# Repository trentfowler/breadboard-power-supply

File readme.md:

# Breadboard power supply

**Description:** Breadboard power supply that delivers 3.3v/5v

BOM - https://www.digikey.com/short/pfpr05

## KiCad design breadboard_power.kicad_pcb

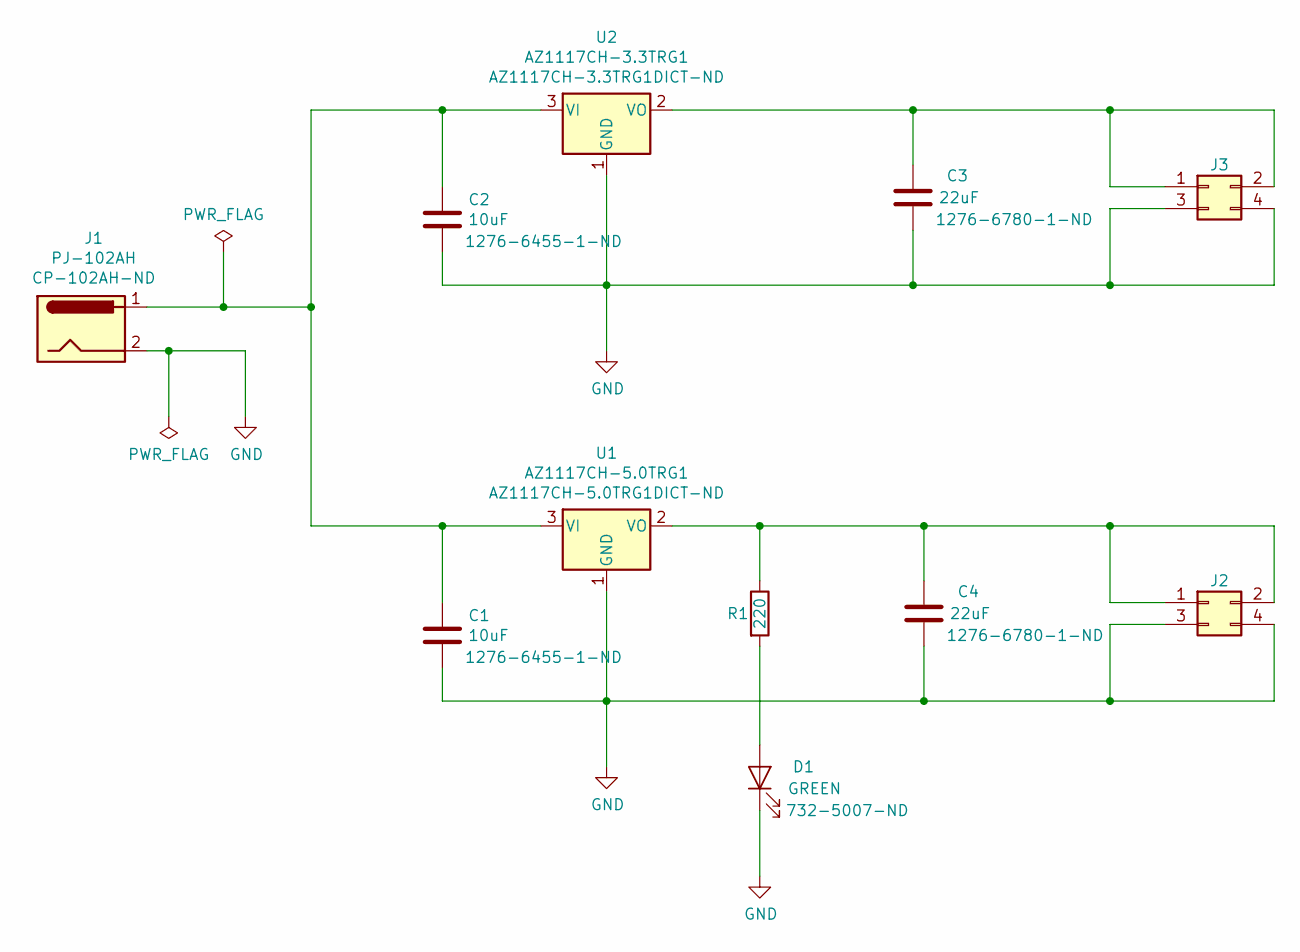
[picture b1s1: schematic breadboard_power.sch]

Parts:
C1, C2: 10uF; C_0805_2012Metric_Pad1.15x1.40mm_HandSolder; digikey 1276-6455-1-ND
C3, C4: 22uF; C_0805_2012Metric_Pad1.15x1.40mm_HandSolder; digikey 1276-6780-1-ND
D1: GREEN; LED_D3.0mm; digikey 732-5007-ND
J1: PJ-102AH; BarrelJack_CUI_PJ-102AH_Horizontal; digikey CP-102AH-ND
J2, J3: Conn_02x02_Odd_Even; PinHeader_2x02_P2.54mm_Vertical
R1: 220; R_0805_2012Metric_Pad1.15x1.40mm_HandSolder
U1: AZ1117CH-5.0TRG1; SOT-223-3_TabPin2; digikey AZ1117CH-5.0TRG1DICT-ND
U2: AZ1117CH-3.3TRG1; SOT-223-3_TabPin2; digikey AZ1117CH-3.3TRG1DICT-ND

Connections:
GND: C1.2, C2.2, C3.2, C4.2, D1.1 (K), J1.2, J2.3, J2.4, J3.3, J3.4, U1.1 (GND), U2.1 (GND)
unnamed: C1.1, C2.1, J1.1, U1.3 (VI), U2.3 (VI)
unnamed: C3.1, J3.1, J3.2, U2.2 (VO)
unnamed: C4.1, J2.1, J2.2, R1.1, U1.2 (VO)
unnamed: D1.2 (A), R1.2

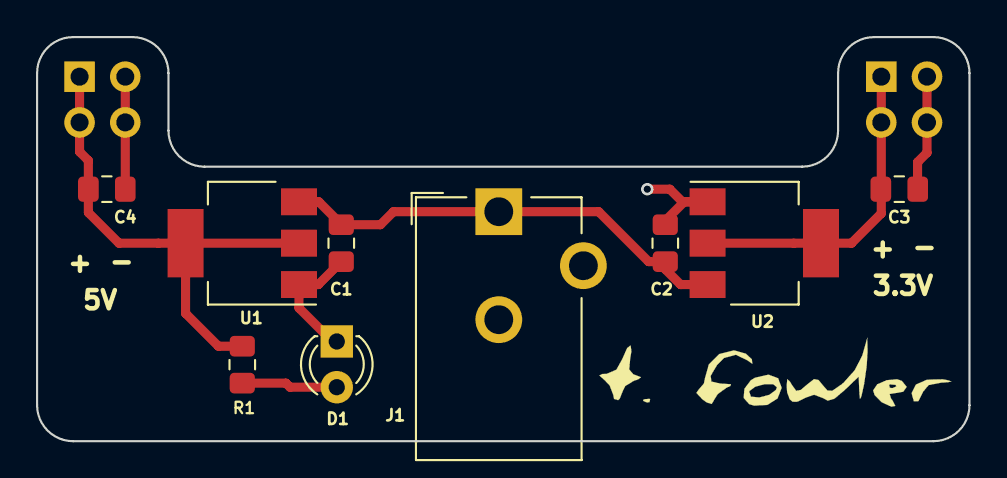
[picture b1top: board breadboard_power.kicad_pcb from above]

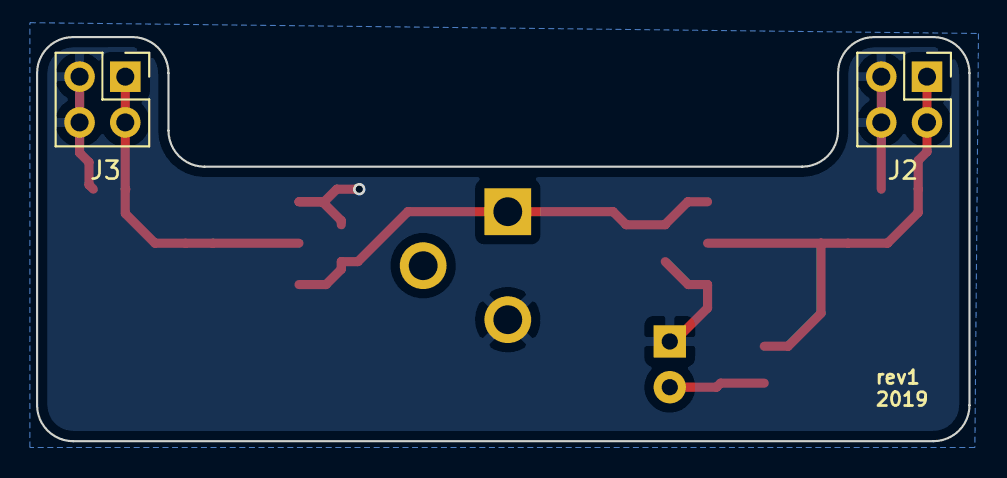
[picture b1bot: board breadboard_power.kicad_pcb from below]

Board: 2 copper layers, 51.8 x 22.4 mm, 11 parts (2 on the bottom side), 5 nets.

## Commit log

2019-09-13 Add micro usb (digikey 609-4618-1-ND) component symbol
